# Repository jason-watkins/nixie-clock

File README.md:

[![CC BY-SA 4.0][cc-by-sa-shield]][cc-by-sa]

# Nixie Clock

USB-C powered nixie tube clock. Four IN-12B digits, two INS-1 colon lamps, K155ID1 BCD decoder/drivers.

## Boards

### Clock Face

### 170V Flyback converter

## Power

USB-PD negotiates 5-12V supply and feeds it into 3 converters:

- Flyback boost: 170V for the tube anodes
- 3.3V buck boost for the MCU. Boost exists to make sure a 3.3V FTDI type UART adapter provides the
  full 3.3V to the rail.
- 5V buck for the BCD drivers, bypassed if the source itself is 5V

## Firmware

Written in Rust, bakes in a list of SSID/password pairs at build time, tries
them until one connects, then syncs time from well-known NTP servers and
displays US Pacific time in 24 hour format.

## BCD/Tube Wiring Note

Tube cathodes are not wired to the decoder outputs in numerical order. The layout connects each
cathode to whichever decoder output it reaches most directly. The K155ID1's output order around its
package does not match the IN-12B's cathode order around its pin circle, so wiring it that way is
more trouble than it's worth. Firmware maps from BCD number to tube number in `nixie::Bcd`.

## Repository layout

- `pcb/` KiCad projects. One project each for the clock face, high voltage flyback converter and the
  main board with the MCU, USB-PD, 3.3V and 5V converters.
- `pcb/lib/` project libraries; origins and local changes in [pcb/lib/README.md](pcb/lib/README.md)
- `firmware/` firmware source code
- `docs/` design doc and vendor datasheets
- `scripts/` [make_release.py](scripts/make_release.py), fab exports with enforced revision bookkeeping

## Fab files

    python scripts/make_release.py --check
    python scripts/make_release.py

Writes gerbers, BOM, and placement files in several formats tailored for
different fab houses under `fab/` and tags the commit. The script's docstring
explains the revision rules it enforces.

## Credits

The K155ID1 symbol and its DIP16 footprint started as imports from
[judge2005's Eagle-and-KiCAD-Nixie-Libs](https://github.com/judge2005/Eagle-and-KiCAD-Nixie-Libs)
and were modified here. Full library inventory: [pcb/lib/README.md](pcb/lib/README.md).

## AI use

AI assistance is used to write and edit documentation, build symbols/footprints, and as a sounding
board for design work. All schematic drawing, PCB layout and code is done by hand.

## License

This work is licensed under a
[Creative Commons Attribution-ShareAlike 4.0 International License][cc-by-sa].

[![CC BY-SA 4.0][cc-by-sa-image]][cc-by-sa]

[cc-by-sa]: http://creativecommons.org/licenses/by-sa/4.0/
[cc-by-sa-image]: https://licensebuttons.net/l/by-sa/4.0/88x31.png
[cc-by-sa-shield]: https://img.shields.io/badge/License-CC%20BY--SA%204.0-lightgrey.svg

except for third-party material carrying its own terms:

- `docs/datasheets/` — manufacturer datasheets and scanned Soviet tube
  documentation, redistributed for reference; sources in
  [docs/tube_notes.md](docs/tube_notes.md).
- `docs/design_analysis/fonts/` — PT Serif and IBM Plex Mono, under the SIL
  Open Font License 1.1.
- The K155ID1 symbol and DIP16 footprint, from judge2005 (no license stated,
  used with attribution); the manufacturer 3D models in
  `pcb/lib/nixie_clock.3dshapes/`; and the section data in
  `cad/ins1/shoulder_profile.py`, sampled from a third-party model. Provenance
  in [pcb/lib/README.md](pcb/lib/README.md).

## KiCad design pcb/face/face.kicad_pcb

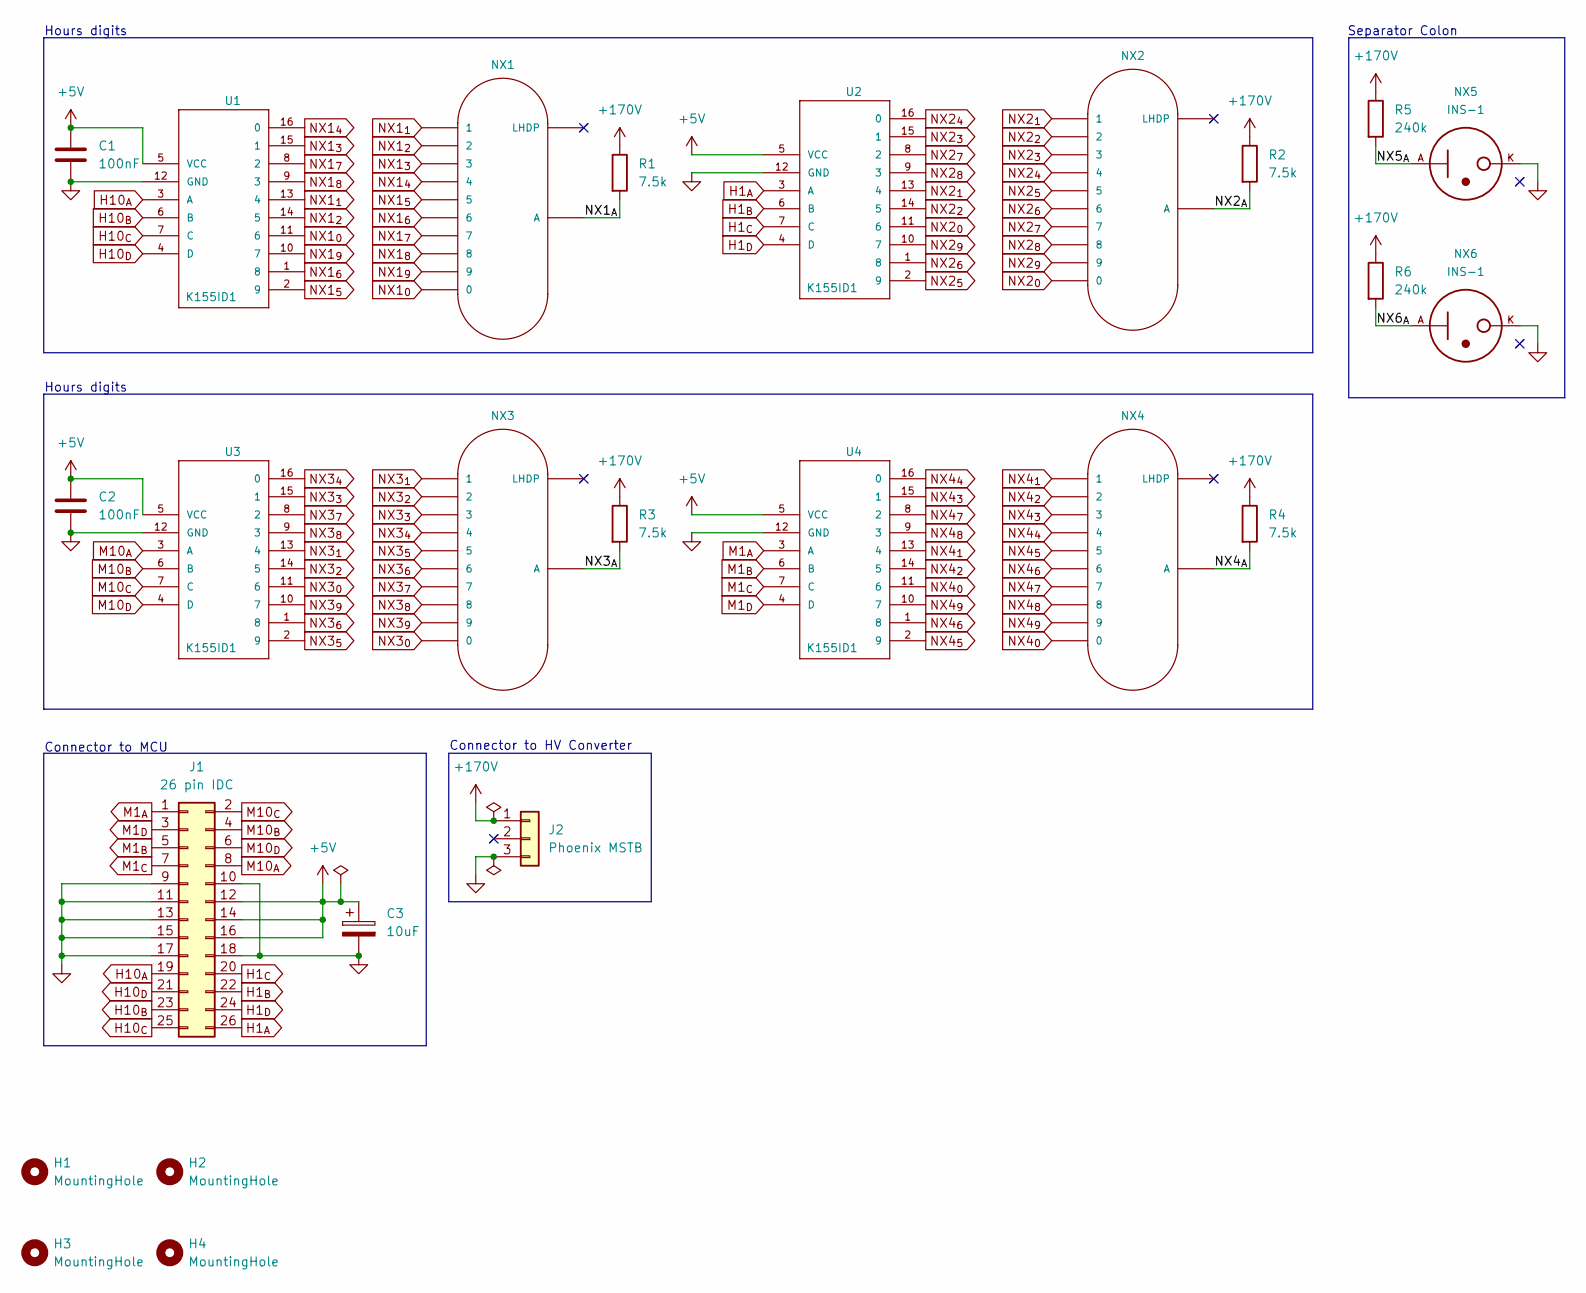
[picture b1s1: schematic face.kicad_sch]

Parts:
C1, C2: 100nF; C_Rect_L5.1mm_W3.2mm_P2.54mm_Goldmax; MFG Part No C320C104K5R5TA
C3: 10uF; CP_Radial_D5.0mm_P2.00mm; MFG Part No A758BG106M1EAAE070
H1, H2, H3, H4: MountingHole; MountingHole_3.2mm_M3_ISO7380
J1: 26 pin IDC; IDC-Header_2x13_P2.54mm_Vertical; MFG Part No 75869-105LF
J2: Phoenix MSTB; PhoenixContact_MSTBVA_2,5_3-G-5,08_1x03_P5.08mm_Vertical; MFG Part No 1755749
NX1, NX2, NX3, NX4: IN-12B; IN-12-DSUB
NX5, NX6: INS-1; INS-1_Recessed
R1, R2, R3, R4: 7.5k; R_Axial_DIN0207_L6.3mm_D2.5mm_P10.16mm_Horizontal; MFG Part No MFR-25FTE52-7K5
R5, R6: 240k; R_Axial_DIN0207_L6.3mm_D2.5mm_P10.16mm_Horizontal; MFG Part No CFR-25JR-52-240K
U1, U2, U3, U4: K155ID1; DIP16

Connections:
+5V: C1.1, C2.1, C3.1, J1.12, J1.14, J1.16, U1.5 (VCC), U2.5 (VCC), U3.5 (VCC), U4.5 (VCC)
+170V: J2.1, R1.1, R2.1, R3.1, R4.1, R5.1, R6.1
/NX1_{A}: NX1.A, R1.2
/NX2_{A}: NX2.A, R2.2
/NX3_{A}: NX3.A, R3.2
/NX4_{A}: NX4.A, R4.2
/NX5_{A}: NX5.A, R5.2
/NX6_{A}: NX6.A, R6.2
GND: C1.2, C2.2, C3.2, J1.9, J1.10, J1.11, J1.13, J1.15, J1.17, J1.18, J2.3, NX5.K, NX6.K, U1.12 (GND), U2.12 (GND), U3.12 (GND), U4.12 (GND)
H1_{A}: J1.26, U2.3 (A)
H1_{B}: J1.22, U2.6 (B)
H1_{C}: J1.20, U2.7 (C)
H1_{D}: J1.24, U2.4 (D)
H10_{A}: J1.19, U1.3 (A)
H10_{B}: J1.23, U1.6 (B)
H10_{C}: J1.25, U1.7 (C)
H10_{D}: J1.21, U1.4 (D)
M1_{A}: J1.1, U4.3 (A)
M1_{B}: J1.5, U4.6 (B)
M1_{C}: J1.7, U4.7 (C)
M1_{D}: J1.3, U4.4 (D)
M10_{A}: J1.8, U3.3 (A)
M10_{B}: J1.4, U3.6 (B)
M10_{C}: J1.2, U3.7 (C)
M10_{D}: J1.6, U3.4 (D)
NX1_{0}: NX1.0, U1.11 (6)
NX1_{1}: NX1.1, U1.13 (4)
NX1_{2}: NX1.2, U1.14 (5)
NX1_{3}: NX1.3, U1.15 (1)
NX1_{4}: NX1.4, U1.16 (0)
NX1_{5}: NX1.5, U1.2 (9)
NX1_{6}: NX1.6, U1.1 (8)
NX1_{7}: NX1.7, U1.8 (2)
NX1_{8}: NX1.8, U1.9 (3)
NX1_{9}: NX1.9, U1.10 (7)
NX2_{0}: NX2.0, U2.11 (6)
NX2_{1}: NX2.1, U2.13 (4)
NX2_{2}: NX2.2, U2.14 (5)
NX2_{3}: NX2.3, U2.15 (1)
NX2_{4}: NX2.4, U2.16 (0)
NX2_{5}: NX2.5, U2.2 (9)
NX2_{6}: NX2.6, U2.1 (8)
NX2_{7}: NX2.7, U2.8 (2)
NX2_{8}: NX2.8, U2.9 (3)
NX2_{9}: NX2.9, U2.10 (7)
NX3_{0}: NX3.0, U3.11 (6)
NX3_{1}: NX3.1, U3.13 (4)
NX3_{2}: NX3.2, U3.14 (5)
NX3_{3}: NX3.3, U3.15 (1)
NX3_{4}: NX3.4, U3.16 (0)
NX3_{5}: NX3.5, U3.2 (9)
NX3_{6}: NX3.6, U3.1 (8)
NX3_{7}: NX3.7, U3.8 (2)
NX3_{8}: NX3.8, U3.9 (3)
NX3_{9}: NX3.9, U3.10 (7)
NX4_{0}: NX4.0, U4.11 (6)
NX4_{1}: NX4.1, U4.13 (4)
NX4_{2}: NX4.2, U4.14 (5)
NX4_{3}: NX4.3, U4.15 (1)
NX4_{4}: NX4.4, U4.16 (0)
NX4_{5}: NX4.5, U4.2 (9)
NX4_{6}: NX4.6, U4.1 (8)
NX4_{7}: NX4.7, U4.8 (2)
NX4_{8}: NX4.8, U4.9 (3)
NX4_{9}: NX4.9, U4.10 (7)

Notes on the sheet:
Connector to MCU
Hours digits
Separator Colon
Connector to HV Converter

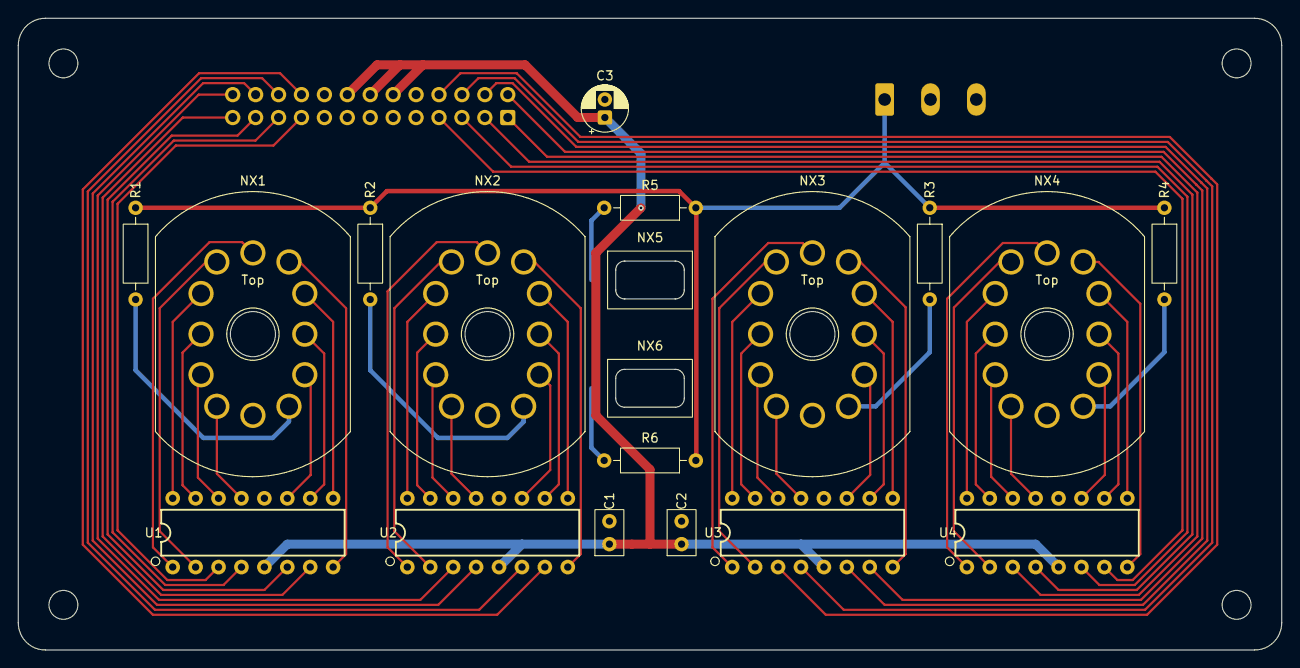
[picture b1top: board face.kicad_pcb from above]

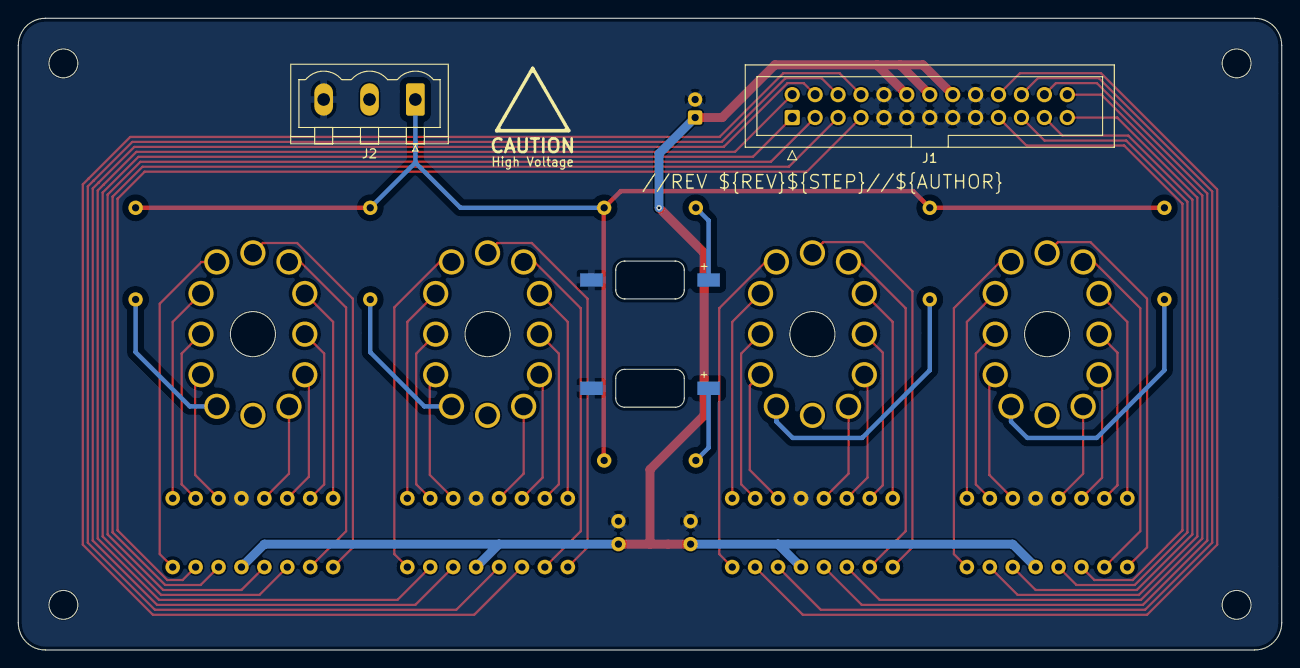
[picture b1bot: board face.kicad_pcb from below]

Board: 2 copper layers, 140.0 x 70.0 mm, 25 parts (2 on the bottom side), 65 nets.

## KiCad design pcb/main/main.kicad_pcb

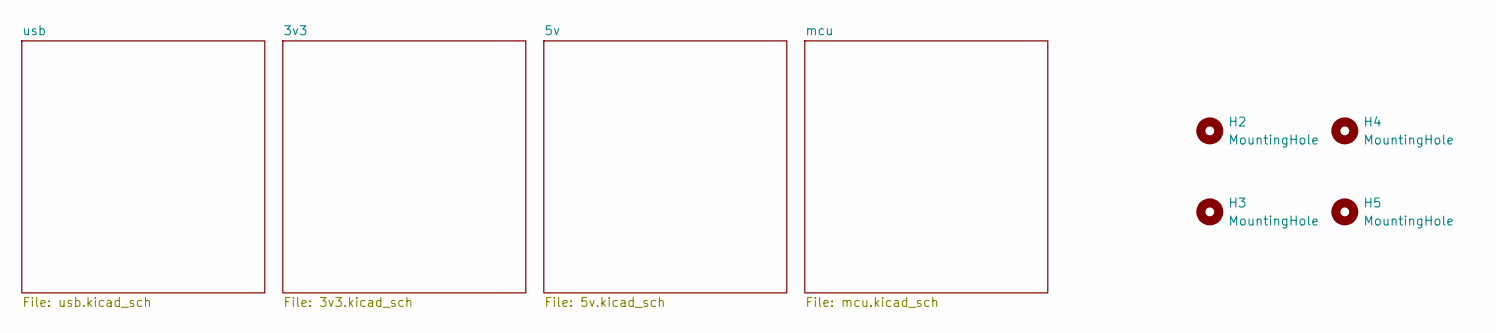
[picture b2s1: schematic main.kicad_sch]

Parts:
H2, H3, H4, H5: MountingHole; MountingHole_3.2mm_M3_ISO7380

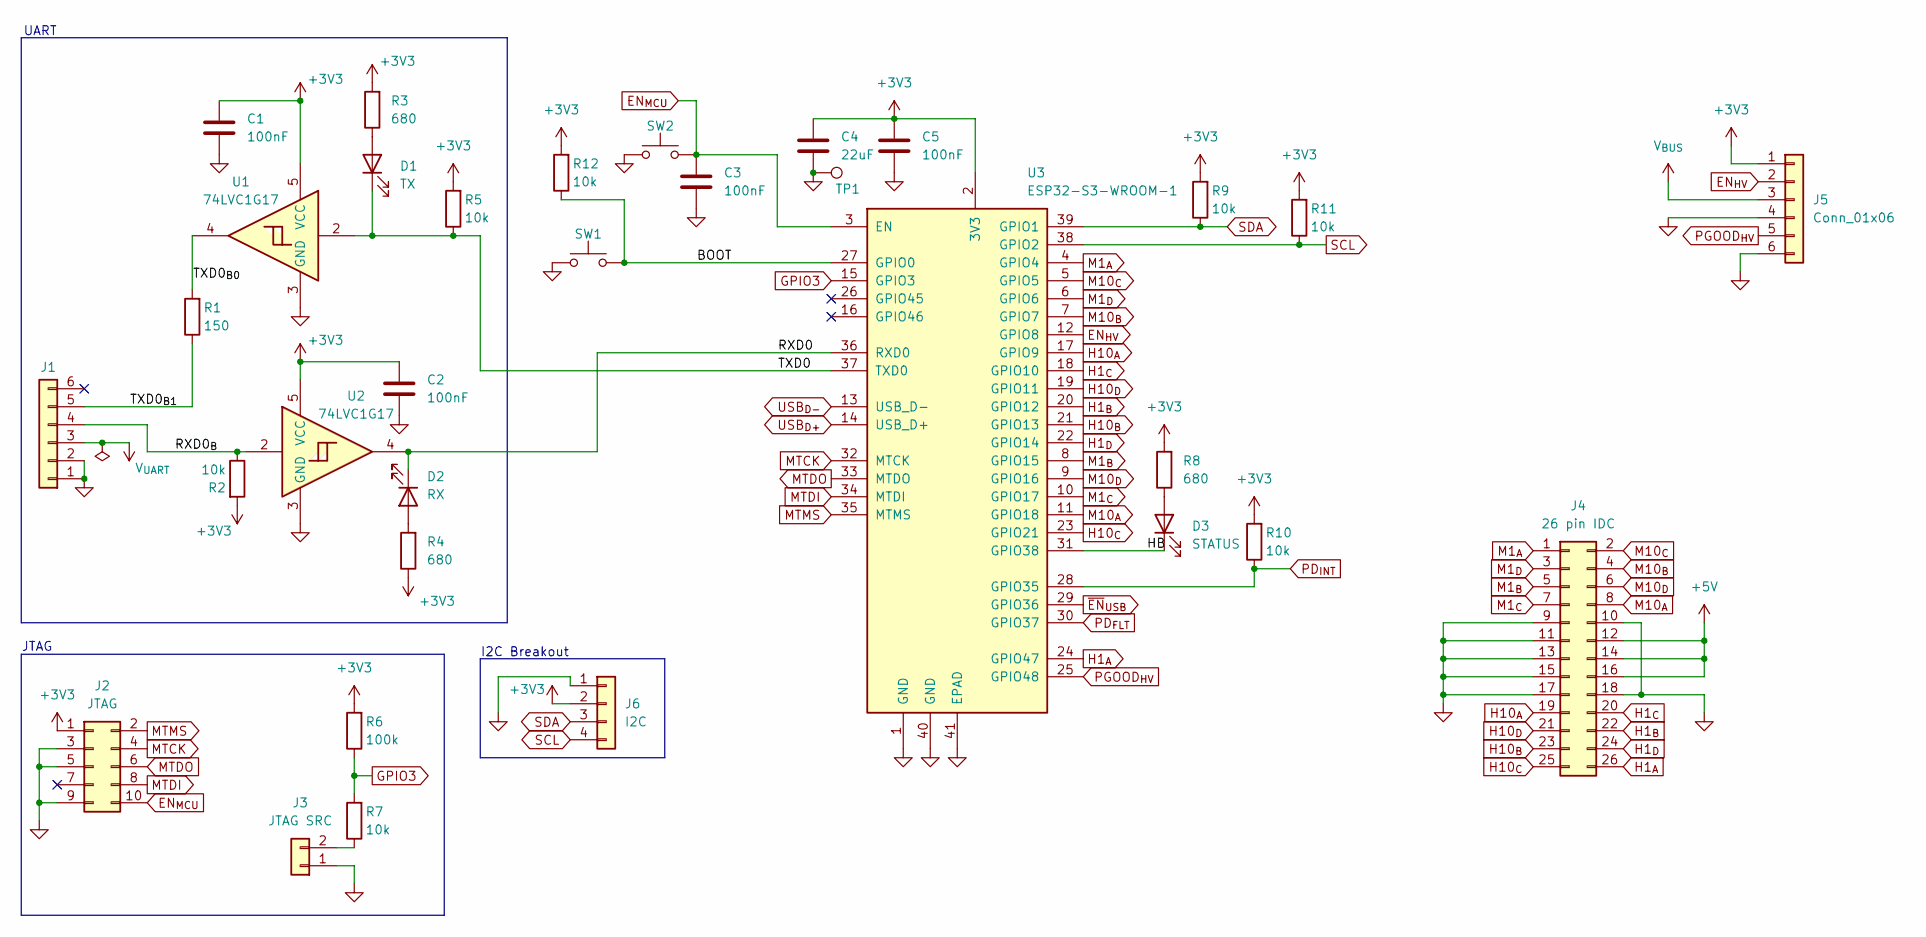
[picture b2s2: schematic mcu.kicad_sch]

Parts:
C1, C2, C3, C5: 100nF; C_0402_1005Metric; MFG Part No CL05B104KB54PNC; LCSC C307331
C4: 22uF; C_1206_3216Metric; MFG Part No CL31A226KPHNNNE; LCSC C5672
D1: TX; LED_0603_1608Metric; MFG Part No NCD0603Y2; LCSC C89811
D2: RX; LED_0603_1608Metric; MFG Part No NCD0603Y2; LCSC C89811
D3: STATUS; LED_0603_1608Metric; MFG Part No NCD0603Y2; LCSC C89811
J1: UART; PinHeader_1x06_P2.54mm_Vertical
J2: JTAG; Samtec_FTSH-105-01-L-DV-K_2x05_P1.27mm_Vertical_SMD; MFG Part No FTSH-105-01-L-DV-K
J3: JTAG SRC; PinHeader_1x02_P1.27mm_Vertical; MFG Part No M50-3530242
J4: 26 pin IDC; IDC-Header_2x13_P2.54mm_Vertical; MFG Part No 75869-105LF
J5: Conn_01x06; JST_XH_S6B-XH-A_1x06_P2.50mm_Horizontal; MFG Part No S6B-XH-A
J6: I2C; PinHeader_1x04_P2.54mm_Vertical
R1: 150; R_0402_1005Metric; MFG Part No RC0402JR-0710KL; LCSC C25082
R2, R9, R10, R11, R12: 10k; R_0402_1005Metric; MFG Part No RC0402JR-0710KL; LCSC C25744
R3, R4, R8: 680; R_0402_1005Metric; MFG Part No 0402WGF6800TCE; LCSC C25130
R5, R7: 10k; R_0402_1005Metric; MFG Part No 0402WGF1002TCE; LCSC C25744
R6: 100k; R_0402_1005Metric; MFG Part No RC0402FR-07100KL; LCSC C25741
SW1: Boot; SW_Panasonic_EVQ_4.9x4.9mm; MFG Part No EVQ-PT9A15
SW2: Reset; SW_Panasonic_EVQ_4.9x4.9mm; MFG Part No EVQ-PT9A15
TP1: GND; TestPoint_Pad_D1.0mm
U1, U2: 74LVC1G17; SOT-23-5; MFG Part No 74LVC1G17GV,125
U3: ESP32-S3-WROOM-1; MFG Part No ESP32-S3-WROOM-1-N8

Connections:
+3V3: C1.1, C2.1, C4.1, C5.1, J2.1, J5.1, J6.2, R2.2, R3.2, R4.1, R5.2, R6.2, R8.2, R9.2, R10.2, R11.2, R12.2, U1.5 (VCC), U2.5 (VCC), U3.2 (3V3); also elsewhere on the board
+5V: J4.12, J4.14, J4.16; also elsewhere on the board
/mcu/BOOT: R12.1, SW1.2, U3.27 (GPIO0)
/mcu/HB: D3.1 (K), U3.31 (GPIO38)
/mcu/RXD0: D2.1 (K), U2.4, U3.36 (RXD0)
/mcu/RXD0_{B}: J1.4, R2.1, U2.2
/mcu/TXD0: D1.1 (K), R5.1, U1.2, U3.37 (TXD0)
/mcu/TXD0_{B0}: R1.2, U1.4
/mcu/TXD0_{B1}: J1.5, R1.1
EN_{HV}: J5.2, U3.12 (GPIO8)
EN_{MCU}: C3.1, J2.10, SW2.2, U3.3 (EN); also elsewhere on the board
GND: C1.2, C2.2, C3.2, C4.2, C5.2, J1.1, J1.2, J2.3, J2.5, J2.9, J3.1, J4.9, J4.10, J4.11, J4.13, J4.15, J4.17, J4.18, J5.4, J5.6, J6.1, SW1.1, SW2.1, TP1.1 (1_1), U1.3 (GND), U2.3 (GND), U3.1 (GND), U3.40 (GND), U3.41 (EPAD); also elsewhere on the board
GPIO3: R6.1, R7.2, U3.15 (GPIO3)
H1_{A}: J4.26, U3.24 (GPIO47)
H1_{B}: J4.22, U3.20 (GPIO12)
H1_{C}: J4.20, U3.18 (GPIO10)
H1_{D}: J4.24, U3.22 (GPIO14)
H10_{A}: J4.19, U3.17 (GPIO9)
H10_{B}: J4.23, U3.21 (GPIO13)
H10_{C}: J4.25, U3.23 (GPIO21)
H10_{D}: J4.21, U3.19 (GPIO11)
M1_{A}: J4.1, U3.4 (GPIO4)
M1_{B}: J4.5, U3.8 (GPIO15)
M1_{C}: J4.7, U3.10 (GPIO17)
M1_{D}: J4.3, U3.6 (GPIO6)
M10_{A}: J4.8, U3.11 (GPIO18)
M10_{B}: J4.4, U3.7 (GPIO7)
M10_{C}: J4.2, U3.5 (GPIO5)
M10_{D}: J4.6, U3.9 (GPIO16)
MTCK: J2.4, U3.32 (MTCK)
MTDI: J2.8, U3.34 (MTDI)
MTDO: J2.6, U3.33 (MTDO)
MTMS: J2.2, U3.35 (MTMS)
unnamed: D1.2 (A), R3.1
unnamed: D2.2 (A), R4.2
unnamed: D3.2 (A), R8.1
unnamed: J3.2, R7.1
PD_{FLT}: U3.30 (GPIO37); also elsewhere on the board
PD_{INT}: R10.1, U3.28 (GPIO35); also elsewhere on the board
PGOOD_{HV}: J5.5, U3.25 (GPIO48)
SCL: J6.4, R11.1, U3.38 (GPIO2); also elsewhere on the board
SDA: J6.3, R9.1, U3.39 (GPIO1); also elsewhere on the board
USB_{D+}: U3.14 (USB_D+); also elsewhere on the board
USB_{D-}: U3.13 (USB_D-); also elsewhere on the board
V_{BUS}: J5.3; also elsewhere on the board
V_{UART}: J1.3; also elsewhere on the board
~EN_{USB}: U3.29 (GPIO36); also elsewhere on the board

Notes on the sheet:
JTAG
UART
I2C Breakout

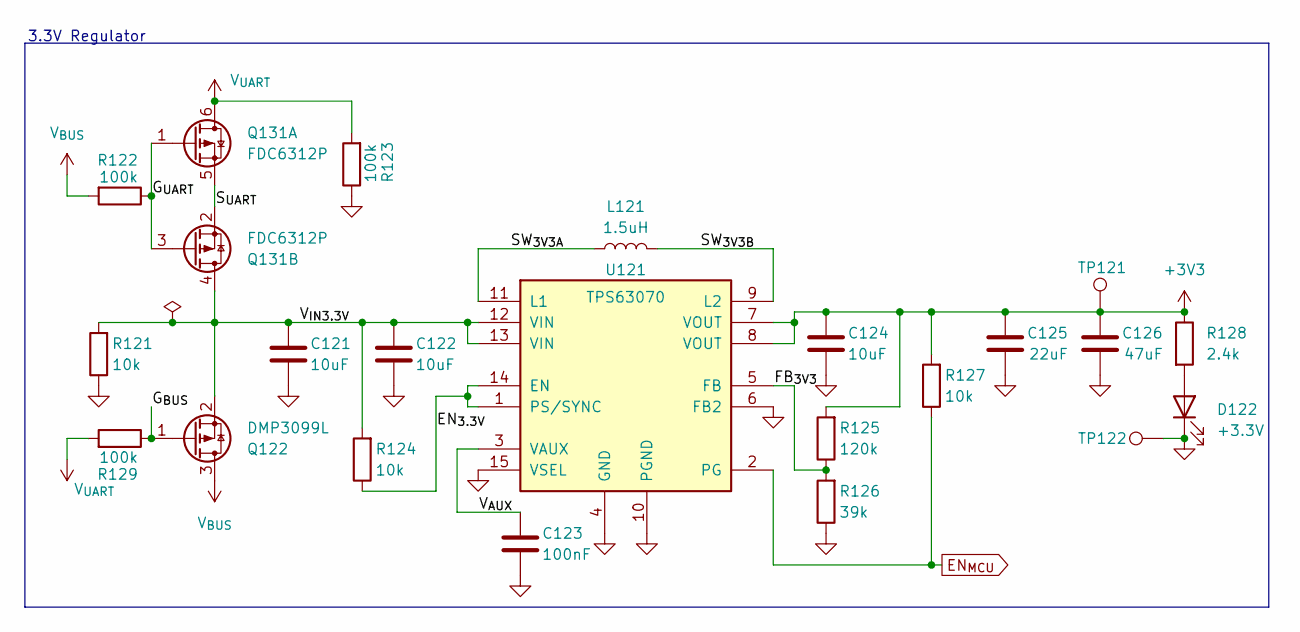
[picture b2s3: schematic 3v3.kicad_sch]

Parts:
C121: 10uF; C_0805_2012Metric; MFG Part No CL21A106KAYNNNE; LCSC C15850
C122: 10uF; C_0603_1608Metric; MFG Part No CL10A106MA8NRNC; LCSC C96446
C123: 100nF; C_0402_1005Metric; MFG Part No CL05B104KB54PNC; LCSC C1525
C124: 10uF; C_0402_1005Metric; MFG Part No CL05A106MQ5NUNC; LCSC C15525
C125: 22uF; C_1206_3216Metric; MFG Part No CL31A226KPHNNNE; LCSC C5672
C126: 47uF; C_1206_3216Metric; MFG Part No CL31A476MPHNNNE; LCSC C96123
D122: +3.3V; LED_0603_1608Metric; MFG Part No KT-0603R; LCSC C2286
L121: 1.5uH; L_Bourns_SRN5040TA; MFG Part No SRN5040TA-1R5M
Q122: DMP3099L; SOT-23-3; MFG Part No DMP3099L-13; LCSC C412516
Q131: FDC6312P; SOT-23-6; MFG Part No FDC6312P; LCSC C241767
R121, R124, R127: 10k; R_0402_1005Metric; MFG Part No 0402WGF1002TCE; LCSC C25744
R122, R129: 100k; R_0402_1005Metric; MFG Part No RC0402FR-07100KL; LCSC C25741
R123: 100k; R_0402_1005Metric; MFG Part No RC0402FR-07100KL; LCSC C60491
R125: 120k; R_0402_1005Metric; MFG Part No 0402WGF1203TCE; LCSC C25750
R126: 39k; R_0402_1005Metric; MFG Part No 0402WGF3902TCE; LCSC C25783
R128: 2.4k; R_0402_1005Metric; MFG Part No 0402WGF2401TCE; LCSC C25882
TP121: +3V3; TestPoint_Pad_D1.0mm
TP122: GND; TestPoint_Pad_D1.0mm
U121: TPS63070; VQFN-15_2.5x3mm_TI_RNM0015A; MFG Part No TPS630702RNMR

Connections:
+3V3: C124.1, C125.1, C126.1, R125.2, R127.2, R128.1, TP121.1 (1_1), U121.7 (VOUT), U121.8 (VOUT); also elsewhere on the board
/3v3/EN_{3.3V}: R124.1, U121.1 (PS/SYNC), U121.14 (EN)
/3v3/FB_{3V3}: R125.1, R126.2, U121.5 (FB)
/3v3/G_{BUS}: Q122.1 (G), R129.1
/3v3/G_{UART}: Q131.1 (G), Q131.3 (G), R122.1
/3v3/SW_{3V3A}: L121.1, U121.11 (L1)
/3v3/SW_{3V3B}: L121.2, U121.9 (L2)
/3v3/S_{UART}: Q131.2 (S), Q131.5 (S)
/3v3/V_{AUX}: C123.1, U121.3 (VAUX)
/3v3/V_{IN3.3V}: C121.1, C122.1, Q122.2 (S), Q131.4 (D), R121.2, R124.2, U121.12 (VIN), U121.13 (VIN)
EN_{MCU}: R127.1, U121.2 (PG); also elsewhere on the board
GND: C121.2, C122.2, C123.2, C124.2, C125.2, C126.2, D122.1 (K), R121.1, R123.1, R126.1, TP122.1 (1_1), U121.4 (GND), U121.6 (FB2), U121.10 (PGND), U121.15 (VSEL); also elsewhere on the board
unnamed: D122.2 (A), R128.2
V_{BUS}: Q122.3 (D), R122.2; also elsewhere on the board
V_{UART}: Q131.6 (D), R123.2, R129.2; also elsewhere on the board

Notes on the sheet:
3.3V Regulator

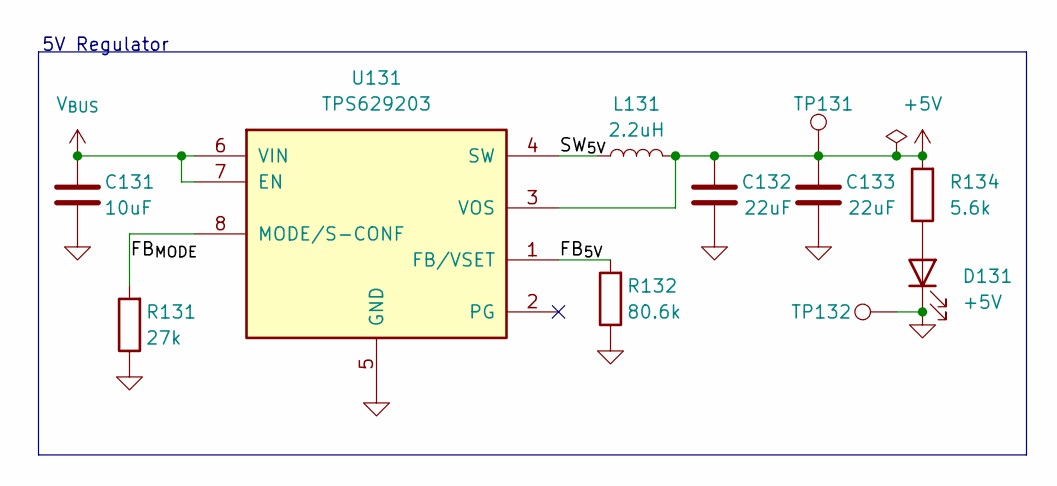
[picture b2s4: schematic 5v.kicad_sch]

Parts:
C131: 10uF; C_0805_2012Metric; MFG Part No CL21A106KAYNNNE; LCSC C15850
C132, C133: 22uF; C_1206_3216Metric; MFG Part No CL31A226KPHNNNE; LCSC C5672
D131: +5V; LED_0603_1608Metric; MFG Part No KT-0603R; LCSC C2286
L131: 2.2uH; L_Bourns_SRN5040TA; MFG Part No SRN5040TA-2R2M
R131: 27k; R_0402_1005Metric; MFG Part No 0402WGF2702TCE; LCSC C25771
R132: 80.6k; R_0402_1005Metric; MFG Part No RC0402FR-0780K6L; LCSC C155698
R134: 5.6k; R_0402_1005Metric; MFG Part No 0402WGF5601TCE; LCSC C25908
TP131: +5V; TestPoint_Pad_D1.0mm
TP132: GND; TestPoint_Pad_D1.0mm
U131: TPS629203; SOT-583-8; MFG Part No TPS629203DRLR

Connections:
+5V: C132.1, C133.1, L131.2, R134.2, TP131.1 (1_1), U131.3 (VOS); also elsewhere on the board
/5v/FB_{5V}: R132.2, U131.1 (FB/VSET)
/5v/FB_{MODE}: R131.2, U131.8 (MODE/S-CONF)
/5v/SW_{5V}: L131.1, U131.4 (SW)
GND: C131.2, C132.2, C133.2, D131.1 (K), R131.1, R132.1, TP132.1 (1_1), U131.5 (GND); also elsewhere on the board
unnamed: D131.2 (A), R134.1
V_{BUS}: C131.1, U131.6 (VIN), U131.7 (EN); also elsewhere on the board

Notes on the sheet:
5V Regulator

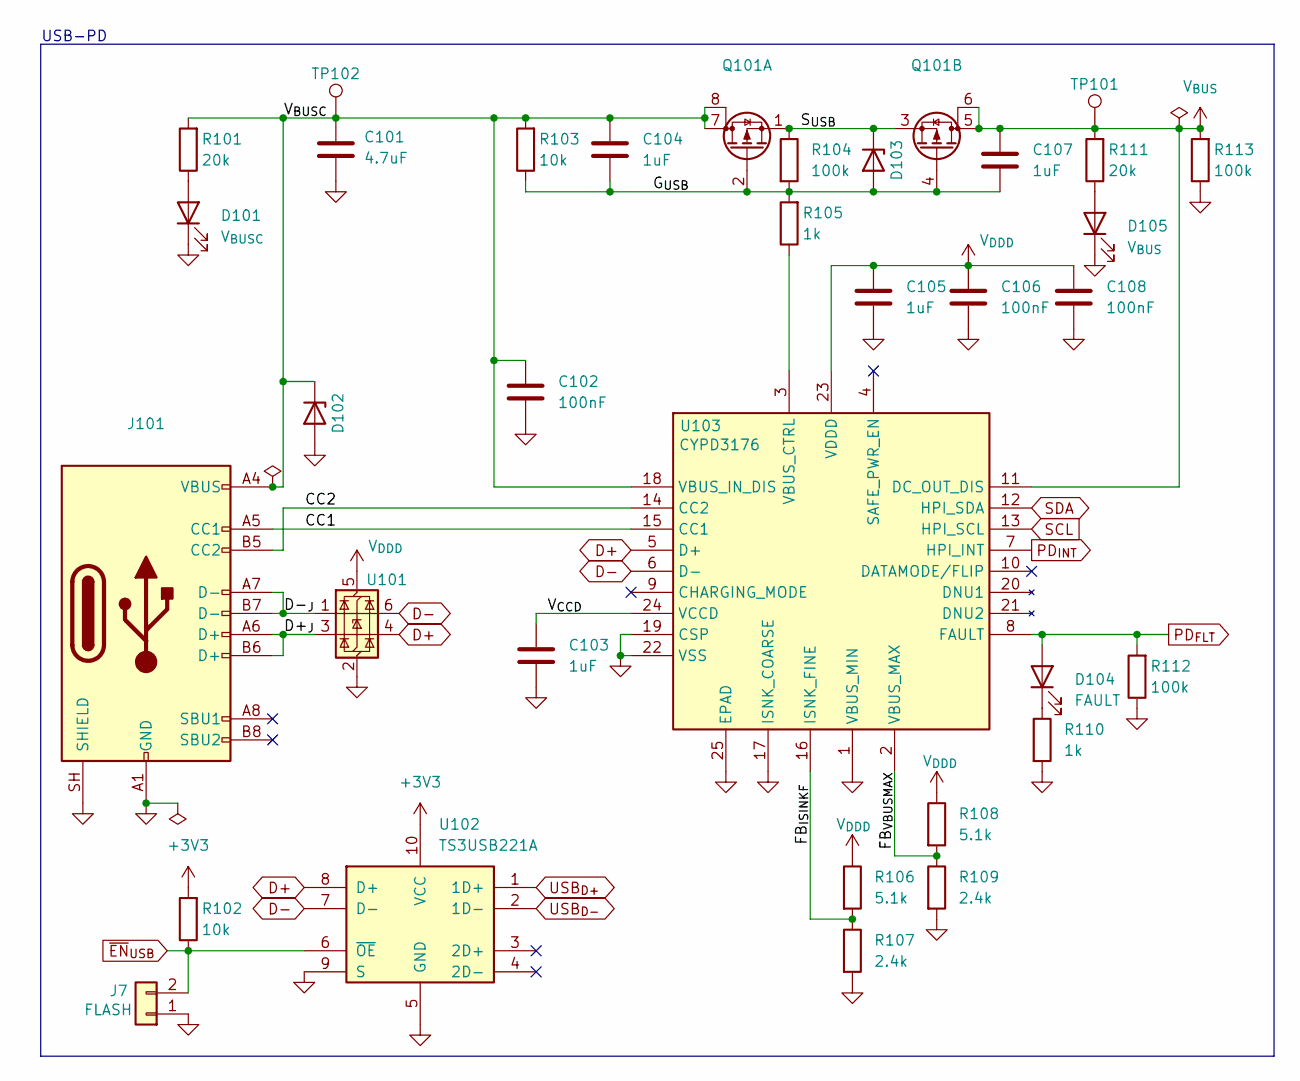
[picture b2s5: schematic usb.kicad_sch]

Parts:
C101: 4.7uF; C_0805_2012Metric; MFG Part No CL21A475KAQNNNE; LCSC C1779
C102, C106, C108: 100nF; C_0402_1005Metric; MFG Part No CL05B104KB54PNC; LCSC C307331
C103, C104, C105, C107: 1uF; C_0402_1005Metric; MFG Part No CL05A105KA5NQNC; LCSC C52923
D101: V_{BUSC}; LED_0603_1608Metric; MFG Part No KT-0603R; LCSC C2286
D102: SD15Q-7; D_SOD-323; MFG Part No SD15Q-7; LCSC C19950473
D103: MM3Z10VST1G; D_SOD-323_HandSoldering; MFG Part No MM3Z10VST1G
D104: FAULT; LED_0603_1608Metric; MFG Part No KT-0603R; LCSC C2286
D105: V_{BUS}; LED_0603_1608Metric; MFG Part No KT-0603R; LCSC C2286
J7: FLASH; PinHeader_1x02_P1.27mm_Vertical; MFG Part No M50-3530242
J101: USB_C_Receptacle_USB2.0_16P; USB_C_Receptacle_JAE_DX07S016JA1R1500; MFG Part No DX07S016JA1R1500; LCSC C3197885
Q101: FDS4935A; SOIC-8_3.9x4.9mm_P1.27mm; MFG Part No FDS4935A
R101, R111: 20k; R_0402_1005Metric; MFG Part No RC0402FR-0720KL; LCSC C25765
R102, R103: 10k; R_0402_1005Metric; MFG Part No RC0402JR-0710KL; LCSC C25744
R104, R113: 100k; R_0402_1005Metric; MFG Part No RC0402FR-07100KL; LCSC C25741
R105, R110: 1k; R_0402_1005Metric; MFG Part No 0402WGF1001TCE; LCSC C11702
R106, R108: 5.1k; R_0402_1005Metric; MFG Part No RC0402FR-075K1L; LCSC C25905
R107, R109: 2.4k; R_0402_1005Metric; MFG Part No 0402WGF2401TCE; LCSC C25882
R112: 100k; R_0402_1005Metric; MFG Part No 0402WGF1003TCE; LCSC C25741
TP101: V_{BUS}; TestPoint_Pad_D1.0mm
TP102: VBUS_{C}; TestPoint_Pad_D1.0mm
U101: USBLC6-2SC6; SOT-23-6; MFG Part No USBLC6-2SC6; LCSC C7519
U102: TS3USB221A; UQFN-10_1.5x2mm_P0.5mm_TI_RSE0010A; MFG Part No TS3USB221ARSER; LCSC C128396
U103: CYPD3176; QFN-24-1EP_4x4mm_P0.5mm_EP2.75x2.75mm_ThermalVias; MFG Part No CYPD3176-24LQXQ

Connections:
+3V3: R102.2, U102.10 (VCC); also elsewhere on the board
/usb/CC1: J101.A5 (CC1), U103.15 (CC1)
/usb/CC2: J101.B5 (CC2), U103.14 (CC2)
/usb/D+_{J}: J101.A6 (D+), J101.B6 (D+), U101.3 (I/O2)
/usb/D-_{J}: J101.A7 (D-), J101.B7 (D-), U101.1 (I/O1)
/usb/FB_{ISINKF}: R106.2, R107.1, U103.16 (ISNK_FINE)
/usb/FB_{VBUSMAX}: R108.2, R109.1, U103.2 (VBUS_MAX)
/usb/G_{USB}: C104.2, C107.2, D103.2 (A), Q101.2 (G), Q101.4 (G), R103.1, R104.2, R105.2
/usb/S_{USB}: D103.1 (K), Q101.1 (S), Q101.3 (S), R104.1
/usb/V_{BUSC}: C101.1, C102.1, C104.1, D102.1 (K), J101.A4 (VBUS), J101.A9 (VBUS), J101.B4 (VBUS), J101.B9 (VBUS), Q101.7 (D), Q101.8 (D), R101.2, R103.2, TP102.1 (1_1), U103.18 (VBUS_IN_DIS)
/usb/V_{CCD}: C103.1, U103.24 (VCCD)
D+: U101.4 (I/O2), U102.8 (D+), U103.5 (D+)
D-: U101.6 (I/O1), U102.7 (D-), U103.6 (D-)
GND: C101.2, C102.2, C103.2, C105.2, C106.2, C108.2, D101.1 (K), D102.2 (A), D105.1 (K), J7.1, J101.A1 (GND), J101.A12 (GND), J101.B1 (GND), J101.B12 (GND), J101.SH (SHIELD), R107.2, R109.2, R110.2, R112.1, R113.1, U101.2 (GND), U102.5 (GND), U102.9 (S), U103.1 (VBUS_MIN), U103.17 (ISNK_COARSE), U103.19 (CSP), U103.22 (VSS), U103.25 (EPAD); also elsewhere on the board
unnamed: D101.2 (A), R101.1
unnamed: D104.1 (K), R110.1
unnamed: D105.2 (A), R111.1
unnamed: R105.1, U103.3 (VBUS_CTRL)
PD_{FLT}: D104.2 (A), R112.2, U103.8 (FAULT); also elsewhere on the board
PD_{INT}: U103.7 (HPI_INT); also elsewhere on the board
SCL: U103.13 (HPI_SCL); also elsewhere on the board
SDA: U103.12 (HPI_SDA); also elsewhere on the board
USB_{D+}: U102.1 (1D+); also elsewhere on the board
USB_{D-}: U102.2 (1D-); also elsewhere on the board
V_{BUS}: C107.1, Q101.5 (D), Q101.6 (D), R111.2, R113.2, TP101.1 (1_1), U103.11 (DC_OUT_DIS); also elsewhere on the board
V_{DDD}: C105.1, C106.1, C108.1, R106.1, R108.1, U101.5 (VBUS), U103.23 (VDDD)
~EN_{USB}: J7.2, R102.1, U102.6 (~OE); also elsewhere on the board

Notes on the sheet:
USB-PD

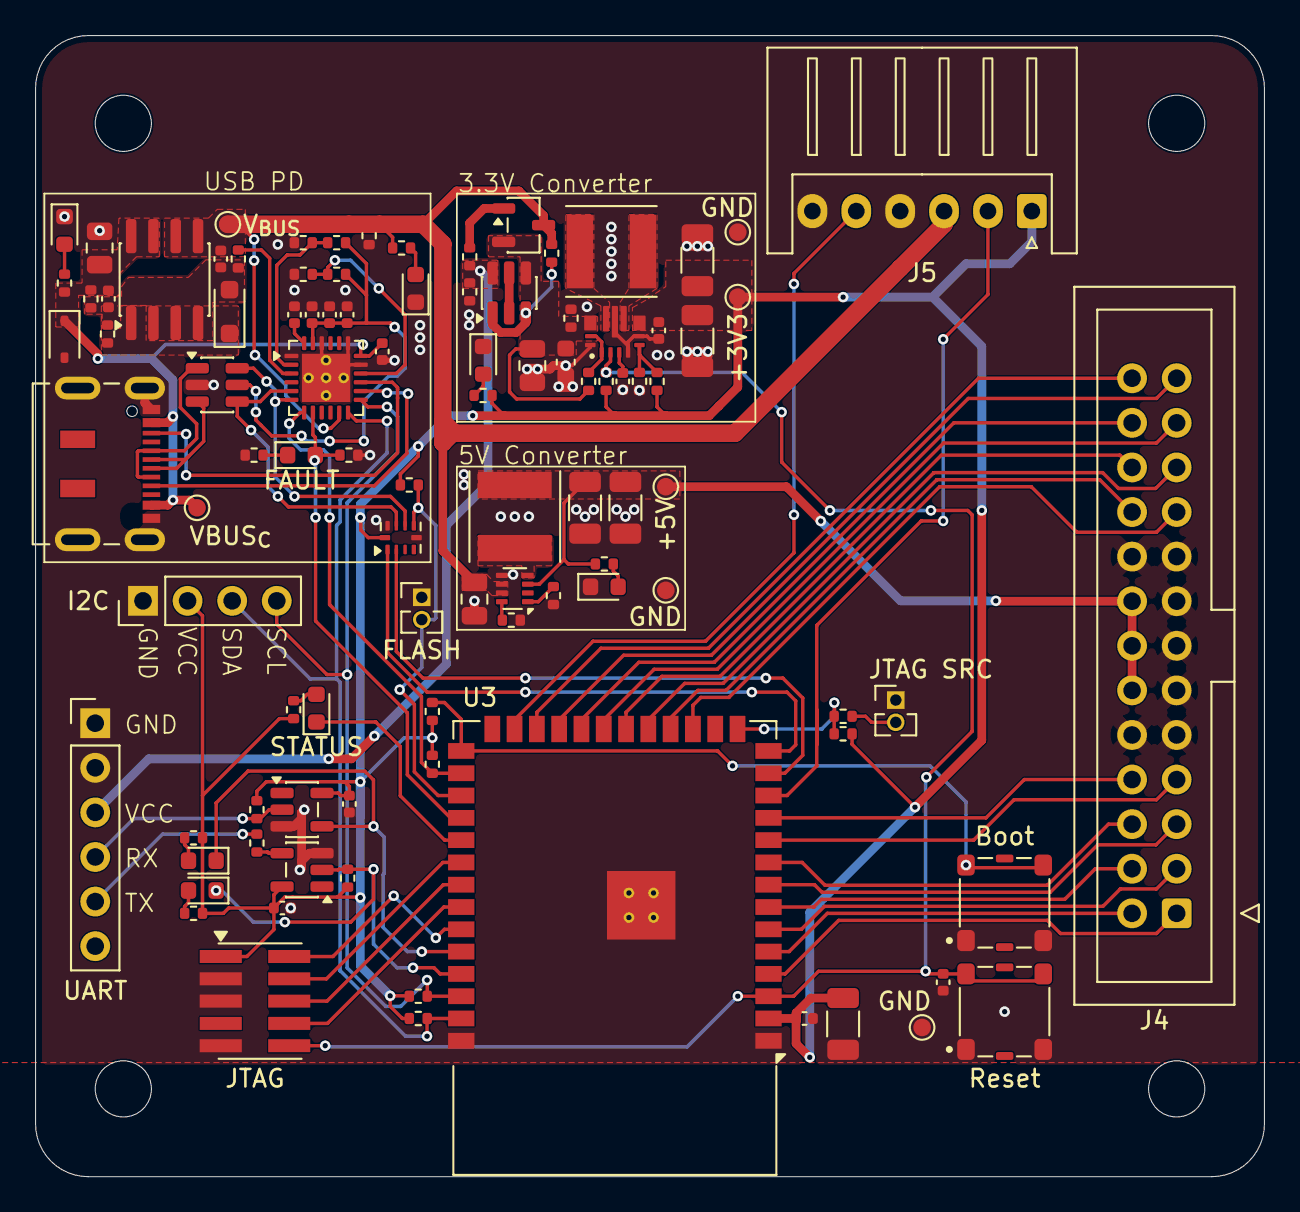
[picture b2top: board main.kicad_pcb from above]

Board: 2 copper layers, 70.0 x 65.0 mm, 103 parts (0 on the bottom side), 78 nets.
